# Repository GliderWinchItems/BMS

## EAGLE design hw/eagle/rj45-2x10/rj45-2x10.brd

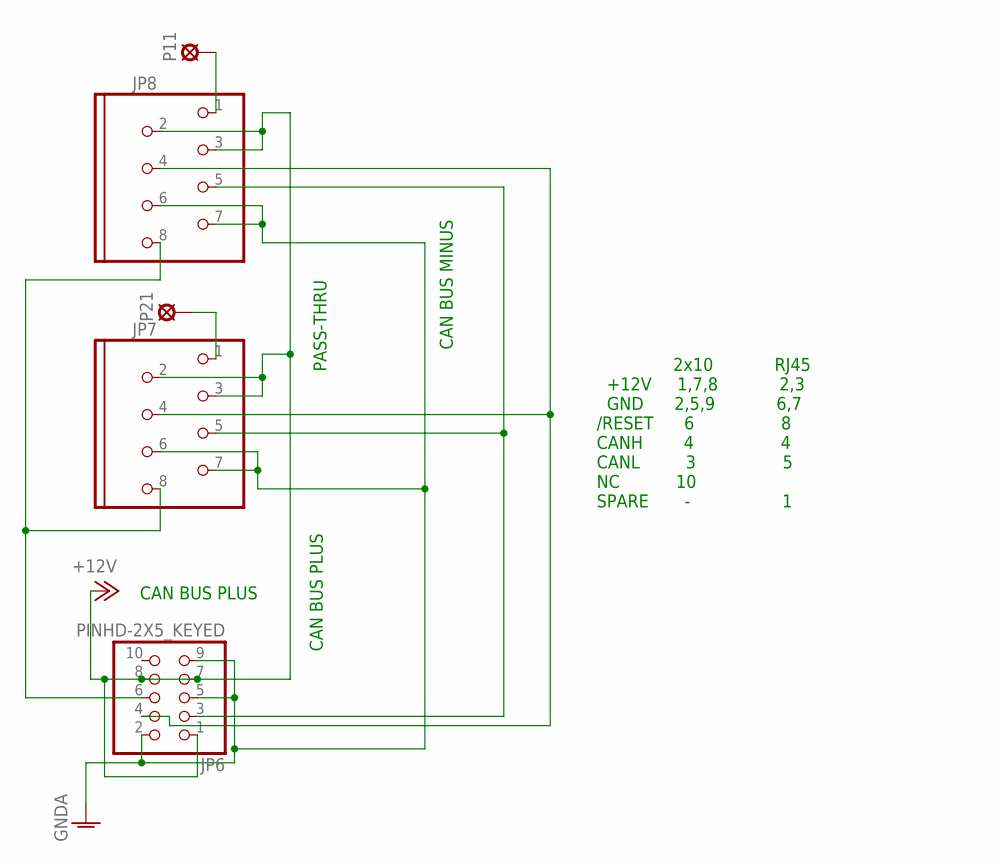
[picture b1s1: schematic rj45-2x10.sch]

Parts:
JP6: PINHD-2X5_KEYED; 2X05_KEYED
JP7, JP8: MOD8P8C
P11, P21: SOLPAD035; SOLDPAD035

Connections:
+12V: JP6.1, JP6.7, JP6.8, JP7.2 (5), JP7.3 (2), JP8.2 (5), JP8.3 (2)
CANCABLE_1_1: JP8.1, P11.MP
CANCABLE_2_1: JP7.1, P21.MP
CANH: JP6.4, JP7.4 (6), JP8.4 (6)
CANL: JP6.3, JP7.5 (3), JP8.5 (3)
GNDA: JP6.2, JP6.5, JP6.9, JP7.6 (7), JP7.7 (4), JP8.6 (7), JP8.7 (4)
MASTER-RESET-SYS: JP6.6, JP7.8, JP8.8

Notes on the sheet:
CAN BUS PLUS
PASS-THRU
CAN BUS MINUS
2x10 RJ45 +12V 1,7,8 2,3 GND 2,5,9 6,7 /RESET 6 8 CANH 4 4 CANL 3 5 NC 10 SPARE - 1

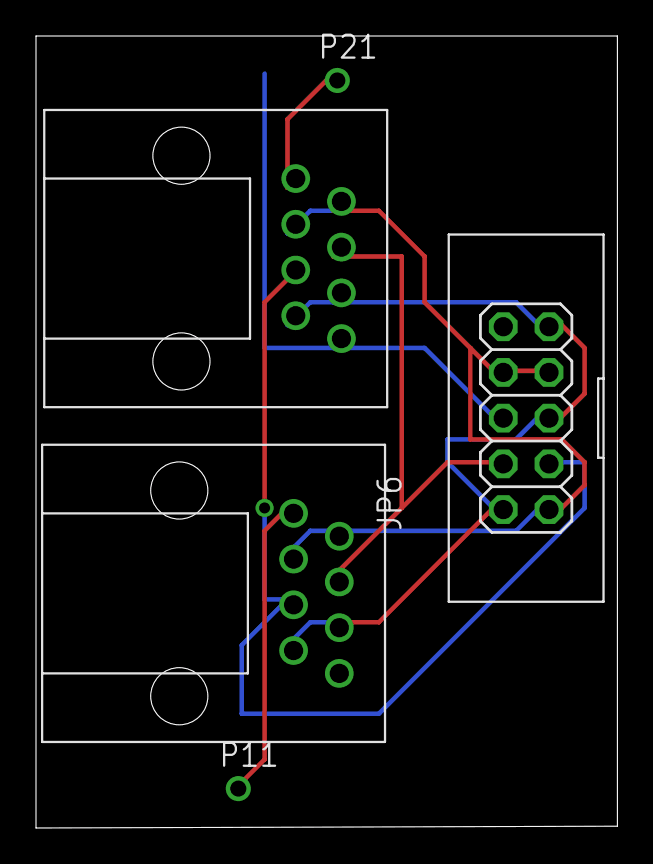
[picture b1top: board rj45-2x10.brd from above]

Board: 2 copper layers, 32.3 x 44.0 mm, 5 parts (0 on the bottom side), 7 nets.
